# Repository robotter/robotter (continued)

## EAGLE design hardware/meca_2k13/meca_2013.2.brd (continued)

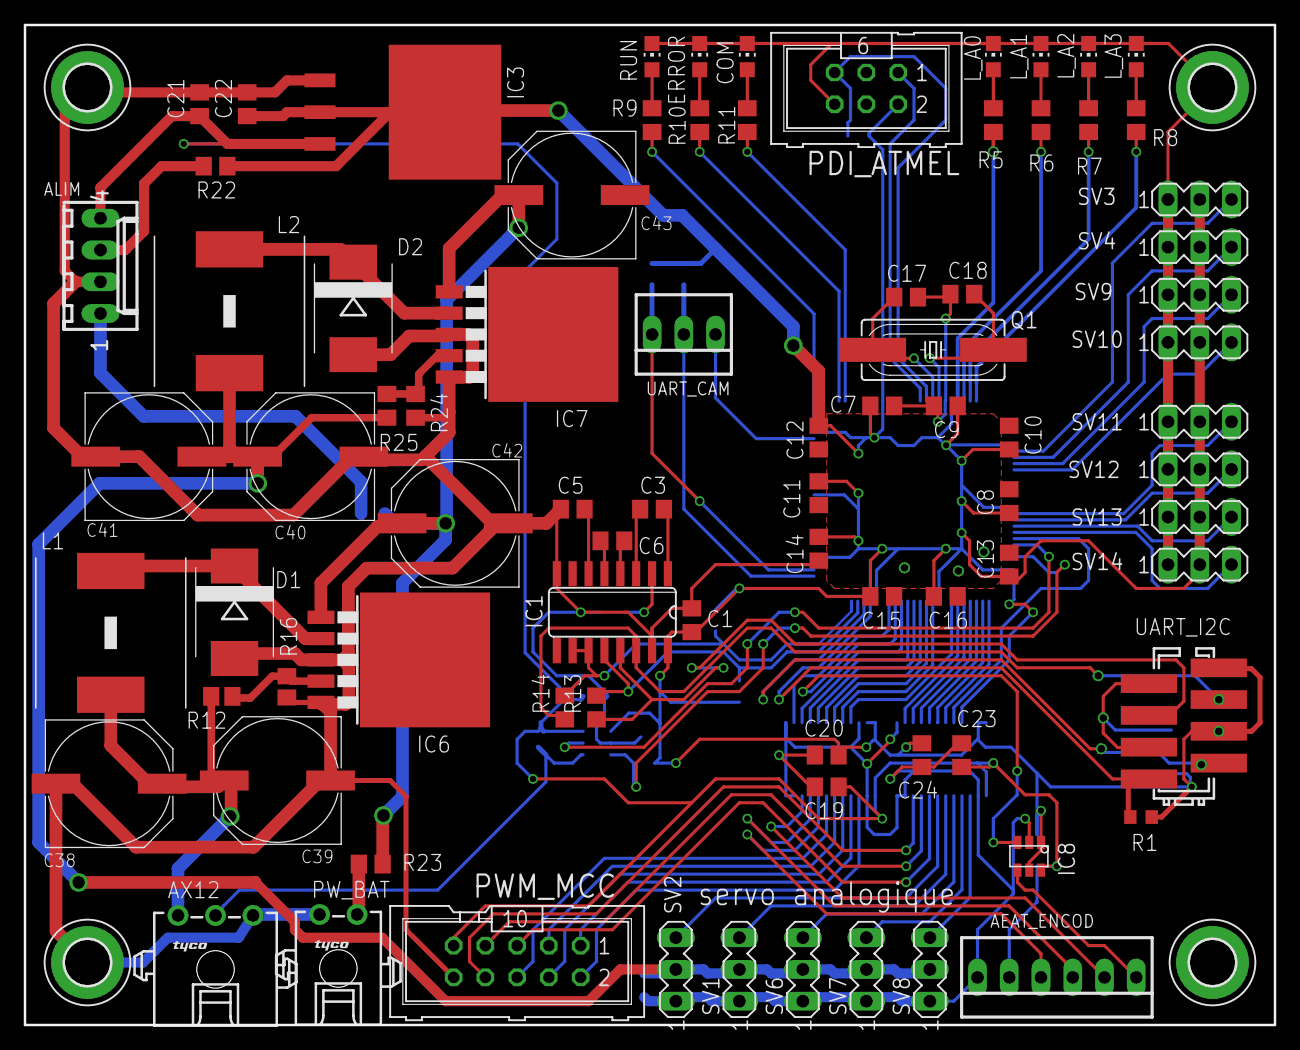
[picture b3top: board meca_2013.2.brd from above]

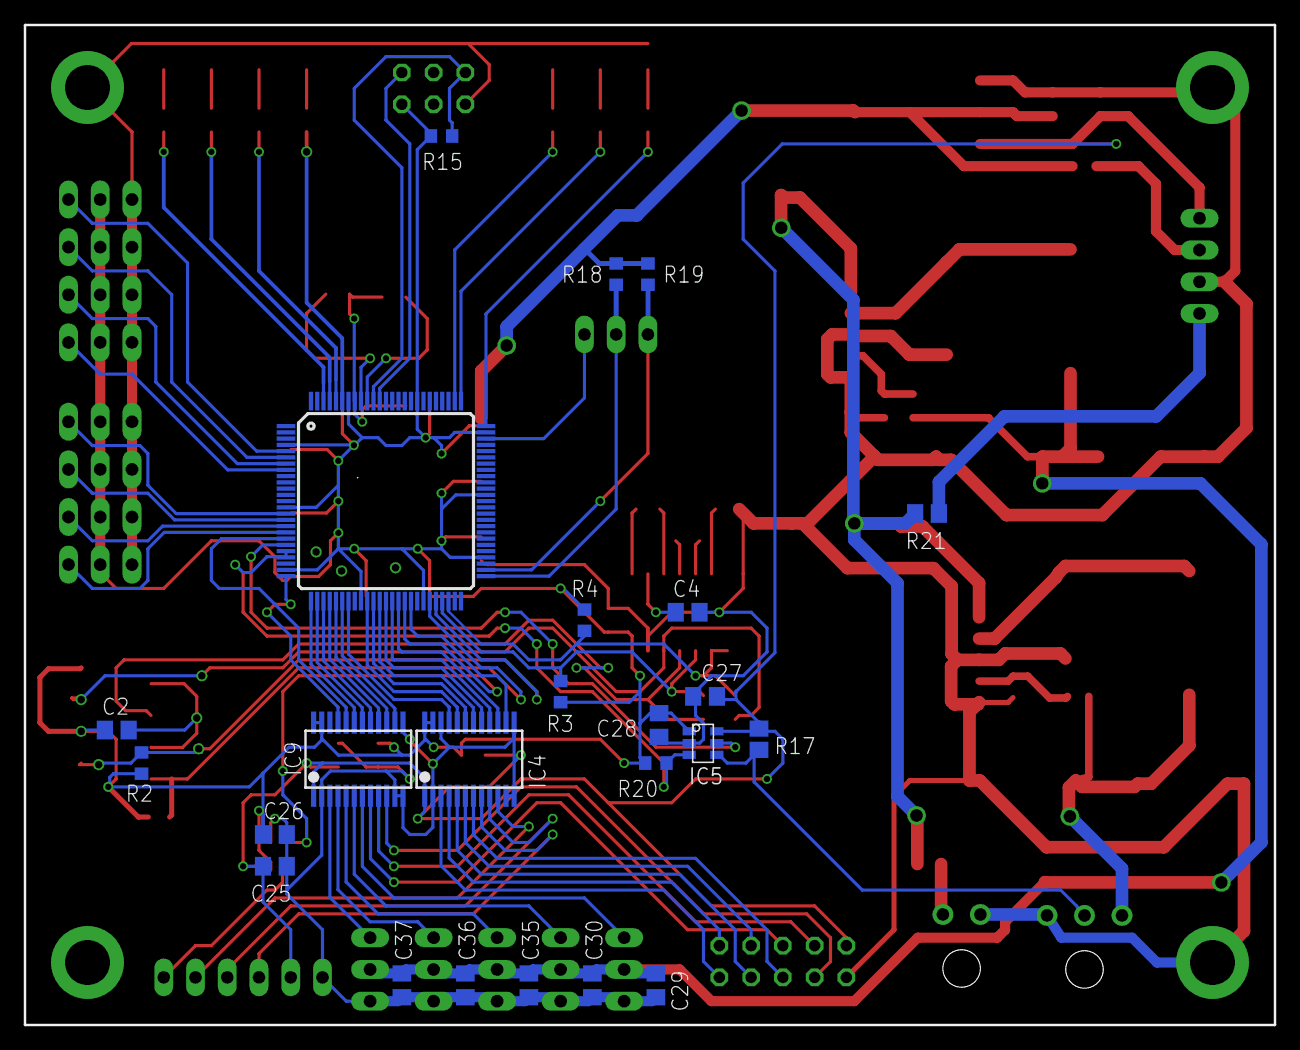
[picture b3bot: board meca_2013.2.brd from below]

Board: 2 copper layers, 100.0 x 80.0 mm, 110 parts (24 on the bottom side), 90 nets.

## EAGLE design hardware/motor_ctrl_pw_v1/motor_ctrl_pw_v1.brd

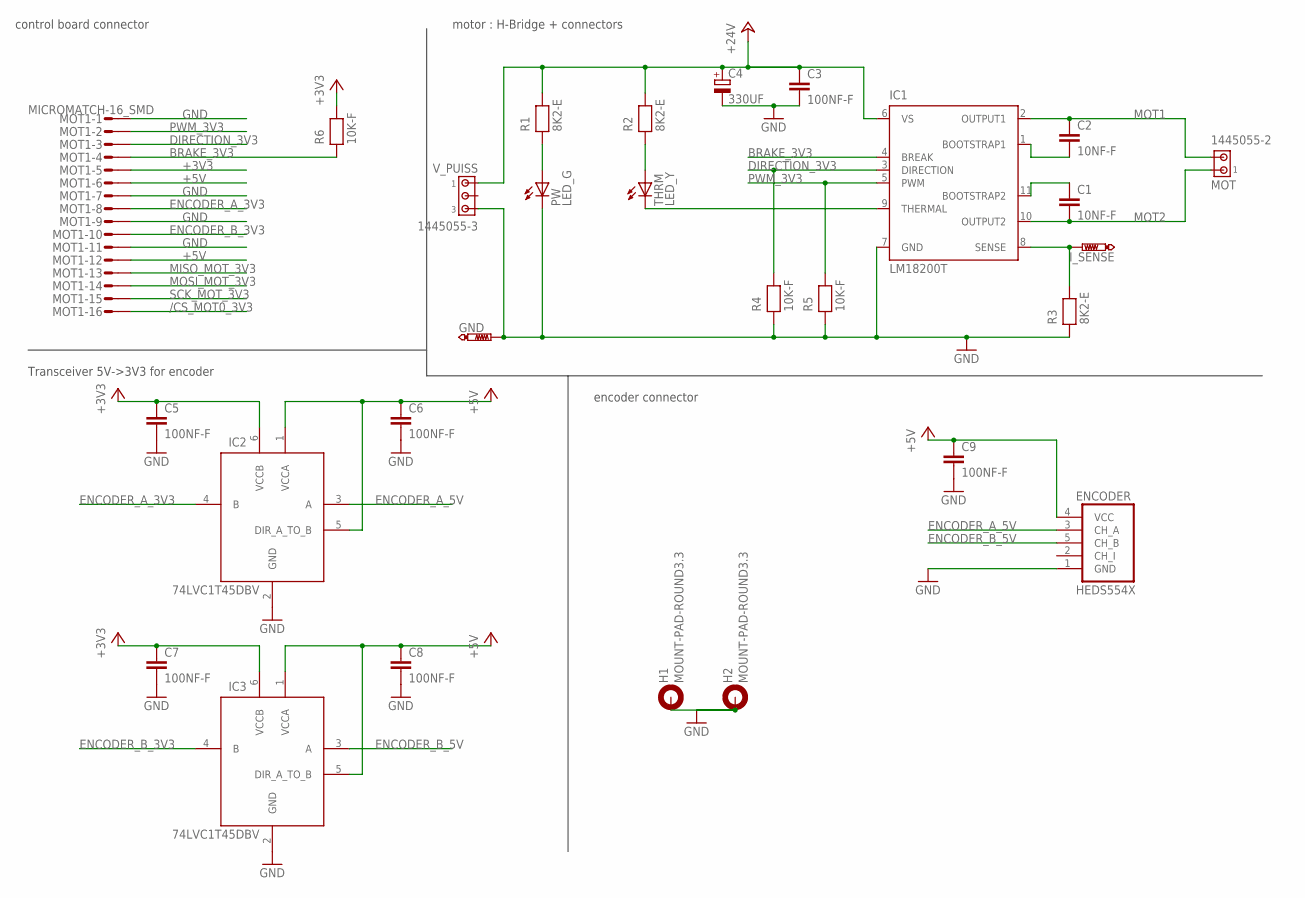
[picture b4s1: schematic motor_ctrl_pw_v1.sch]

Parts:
C1, C2: 10NF-F; C0603
C3, C5, C6, C7, C8, C9: 100NF-F; C0603
C4: 330UF; PANASONIC_G
ENCODER: HEDS554X; 22-05-1052
GND: PTR1PAD1-13; P1-13
H1, H2: MOUNT-PAD-ROUND3.3; 3,3-PAD
IC1: LM18200T; TO-220-11
IC2, IC3: 74LVC1T45DBV; SOT23-6
I_SENSE: PTR1PAD1-13; P1-13
MOT: 1445055-2
MOT1: MICROMATCH-16_SMD
PW: LED_G; CHIP-LED0805
R1, R2, R3: 8K2-E; R0805
R4, R5, R6: 10K-F; R0603
THRM: LED_Y; CHIP-LED0805
V_PUISS: 1445055-3

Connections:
+3V3: C5.1, C7.1, IC2.6 (VCCB), IC3.6 (VCCB), MOT1.5, R6.2
+5V: C6.1, C8.1, C9.1, ENCODER.4 (VCC), IC2.1 (VCCA), IC2.5 (DIR_A_TO_B), IC3.1 (VCCA), IC3.5 (DIR_A_TO_B), MOT1.6, MOT1.12
+24V: C3.1, C4.+, IC1.6 (VS), R1.2, R2.2, V_PUISS.1
/CS_MOT0_3V3: MOT1.16
BRAKE_3V3: IC1.4 (BREAK), MOT1.4, R6.1
DIRECTION_3V3: IC1.3 (DIRECTION), MOT1.3, R4.2
ENCODER_A_3V3: IC2.4 (B), MOT1.8
ENCODER_A_5V: ENCODER.3 (CH_A), IC2.3 (A)
ENCODER_B_3V3: IC3.4 (B), MOT1.10
ENCODER_B_5V: ENCODER.5 (CH_B), IC3.3 (A)
GND: C3.2, C4.-, C5.2, C6.2, C7.2, C8.2, C9.2, ENCODER.1 (GND), GND.TP, H1.B3,3, H2.B3,3, IC1.7 (GND), IC2.2 (GND), IC3.2 (GND), MOT1.1, MOT1.7, MOT1.9, MOT1.11, PW.C, R3.1, R4.1, R5.1, V_PUISS.3
MISO_MOT_3V3: MOT1.13
MOSI_MOT_3V3: MOT1.14
MOT1: C2.1, IC1.2 (OUTPUT1), MOT.2
MOT2: C1.2, IC1.10 (OUTPUT2), MOT.1
unnamed: R2.1, THRM.A
unnamed: IC1.8 (SENSE), I_SENSE.TP, R3.2
unnamed: PW.A, R1.1
unnamed: IC1.9 (THERMAL), THRM.C
unnamed: C2.2, IC1.1 (BOOTSTRAP1)
unnamed: C1.1, IC1.11 (BOOTSTRAP2)
PWM_3V3: IC1.5 (PWM), MOT1.2, R5.2
SCK_MOT_3V3: MOT1.15

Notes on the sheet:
control board connector
motor : H-Bridge + connectors
Transceiver 5V->3V3 for encoder
encoder connector

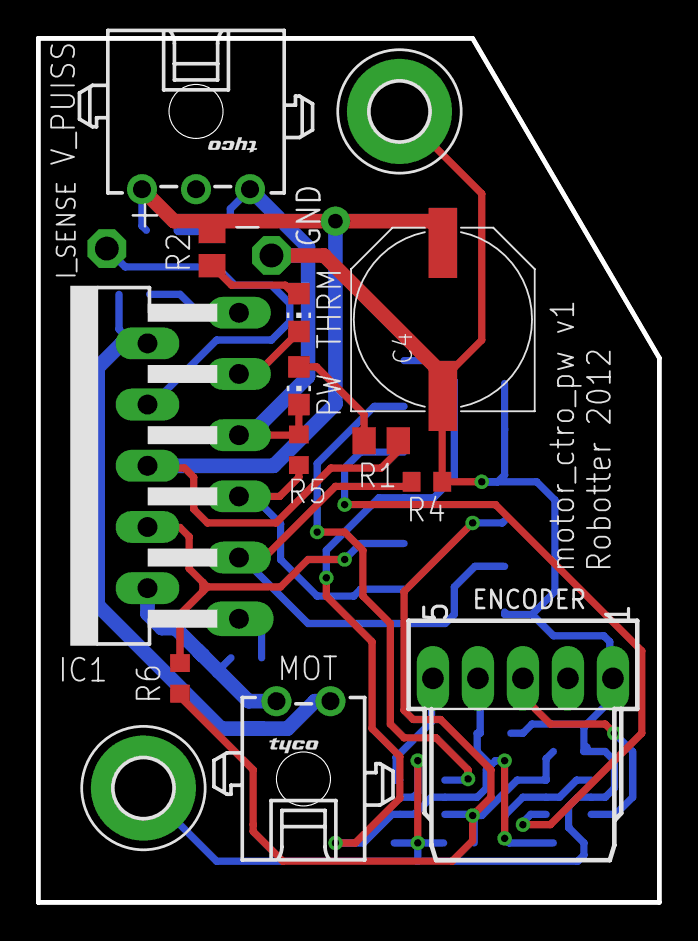
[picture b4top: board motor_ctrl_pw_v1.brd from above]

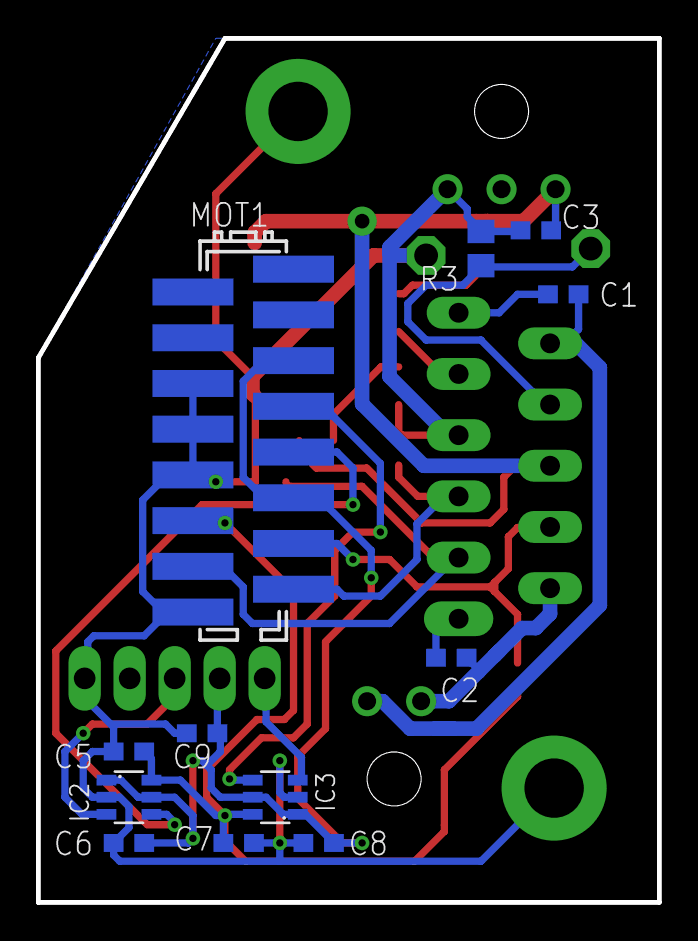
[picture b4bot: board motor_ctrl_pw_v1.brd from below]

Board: 2 copper layers, 34.5 x 48.0 mm, 28 parts (12 on the bottom side), 19 nets.
